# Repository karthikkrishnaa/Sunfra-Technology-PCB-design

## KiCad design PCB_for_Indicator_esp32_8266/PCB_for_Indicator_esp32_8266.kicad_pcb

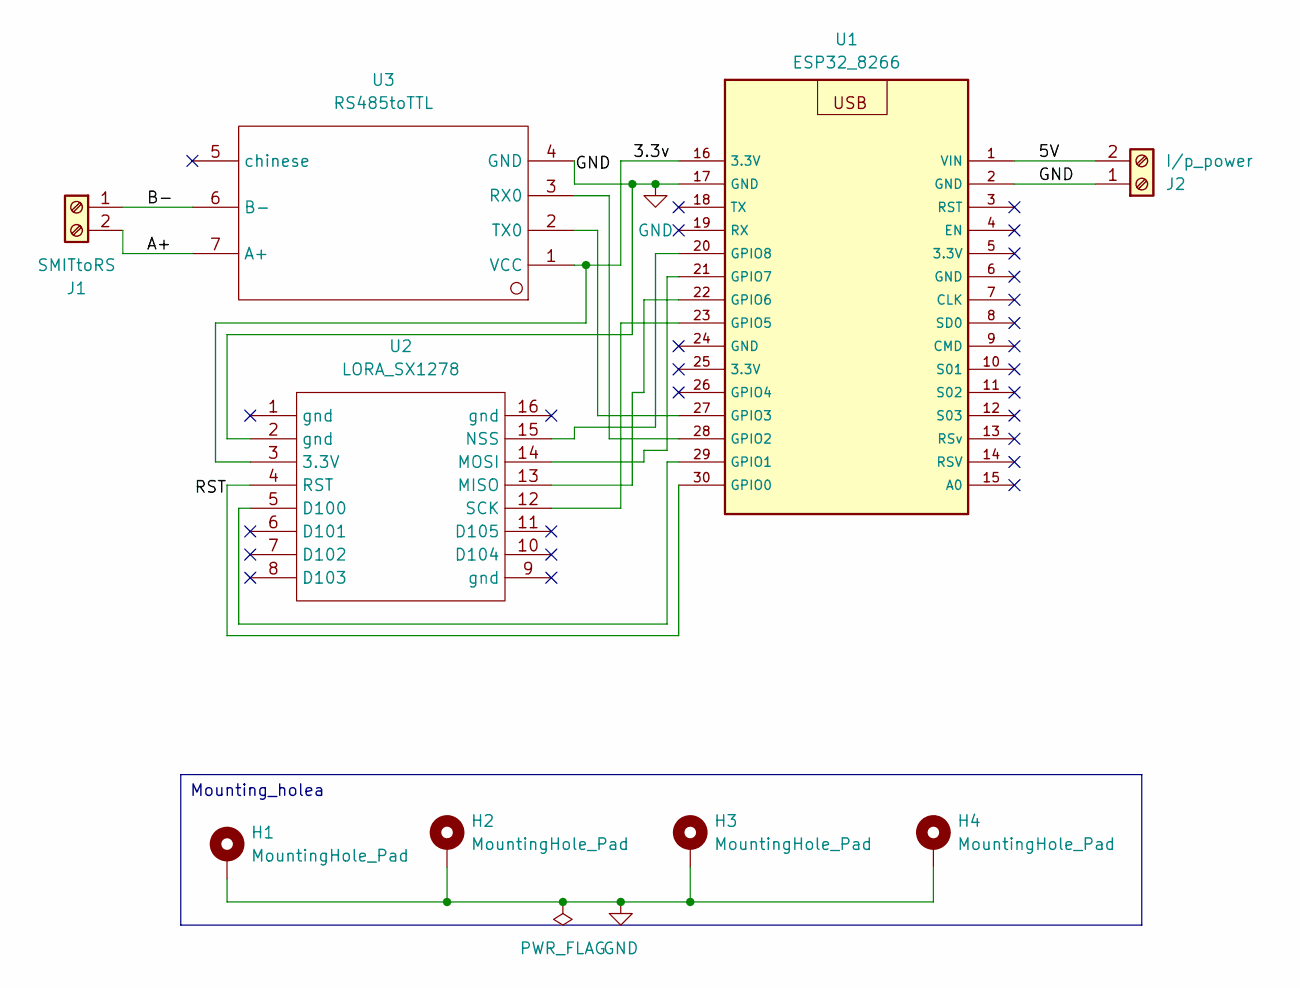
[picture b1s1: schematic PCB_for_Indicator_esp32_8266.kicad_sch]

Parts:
H1, H2, H3, H4: MountingHole_Pad; MountingHole_2.7mm_M2.5_Pad_Via
J1: SMITtoRS; TerminalBlock_Phoenix_MKDS-1,5-2-5.08_1x02_P5.08mm_Horizont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
J2: I/p_power; TerminalBlock_Phoenix_MKDS-1,5-2-5.08_1x02_P5.08mm_Horizont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
U1: ESP32_8266; esp32_node_mcu
U2: LORA_SX1278; LORA_02_SX1278
U3: RS485toTTL; RS485_TTL

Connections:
/3.3v: U1.16 (3.3V), U2.3 (3.3V), U3.1 (VCC)
/5V: J2.2, U1.1 (VIN)
/A+: J1.2, U3.7 (A+)
/B-: J1.1, U3.6 (B-)
/RST: U1.30 (GPIO0), U2.4 (RST)
GND: H1.1 (1_1), H2.1 (1_1), H3.1 (1_1), H4.1 (1_1), J2.1, U1.2 (GND), U1.17 (GND), U2.2 (gnd), U3.4 (GND)
unnamed: U1.29 (GPIO1), U2.5 (D100)
unnamed: U1.28 (GPIO2), U3.3 (RX0)
unnamed: U1.27 (GPIO3), U3.2 (TX0)
unnamed: U1.23 (GPIO5), U2.12 (SCK)
unnamed: U1.22 (GPIO6), U2.13 (MISO)
unnamed: U1.21 (GPIO7), U2.14 (MOSI)
unnamed: U1.20 (GPIO8), U2.15 (NSS)

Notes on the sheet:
Mounting_holea

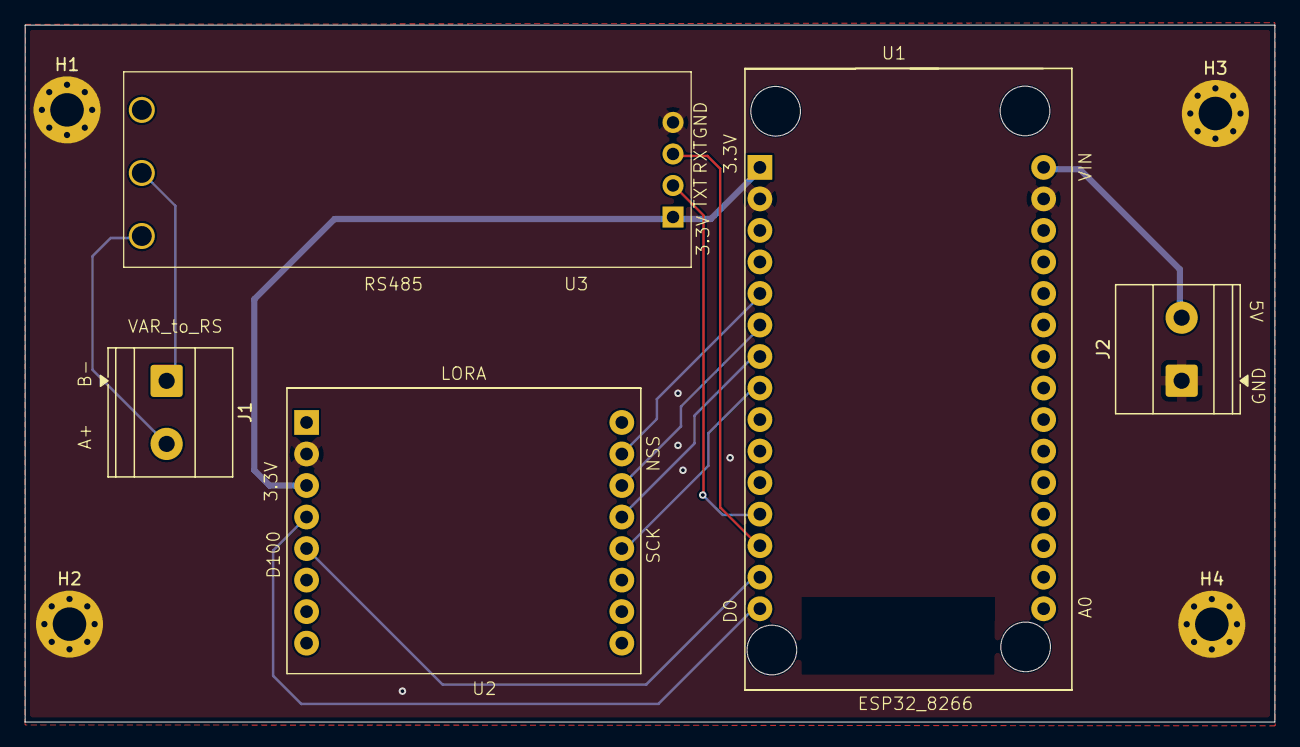
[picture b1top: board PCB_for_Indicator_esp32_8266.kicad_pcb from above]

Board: 2 copper layers, 100.7 x 56.1 mm, 9 parts (0 on the bottom side), 13 nets.

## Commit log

2026-06-22 Initial commit: add all PCB design files
2026-06-22 Add PCB_for_Indicator project files
